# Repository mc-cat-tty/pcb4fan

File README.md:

# pcb4fan

## Schematic

## Render 3D
<p>

 <br>

 <br>
 
</p>

## Etching mask

## Results

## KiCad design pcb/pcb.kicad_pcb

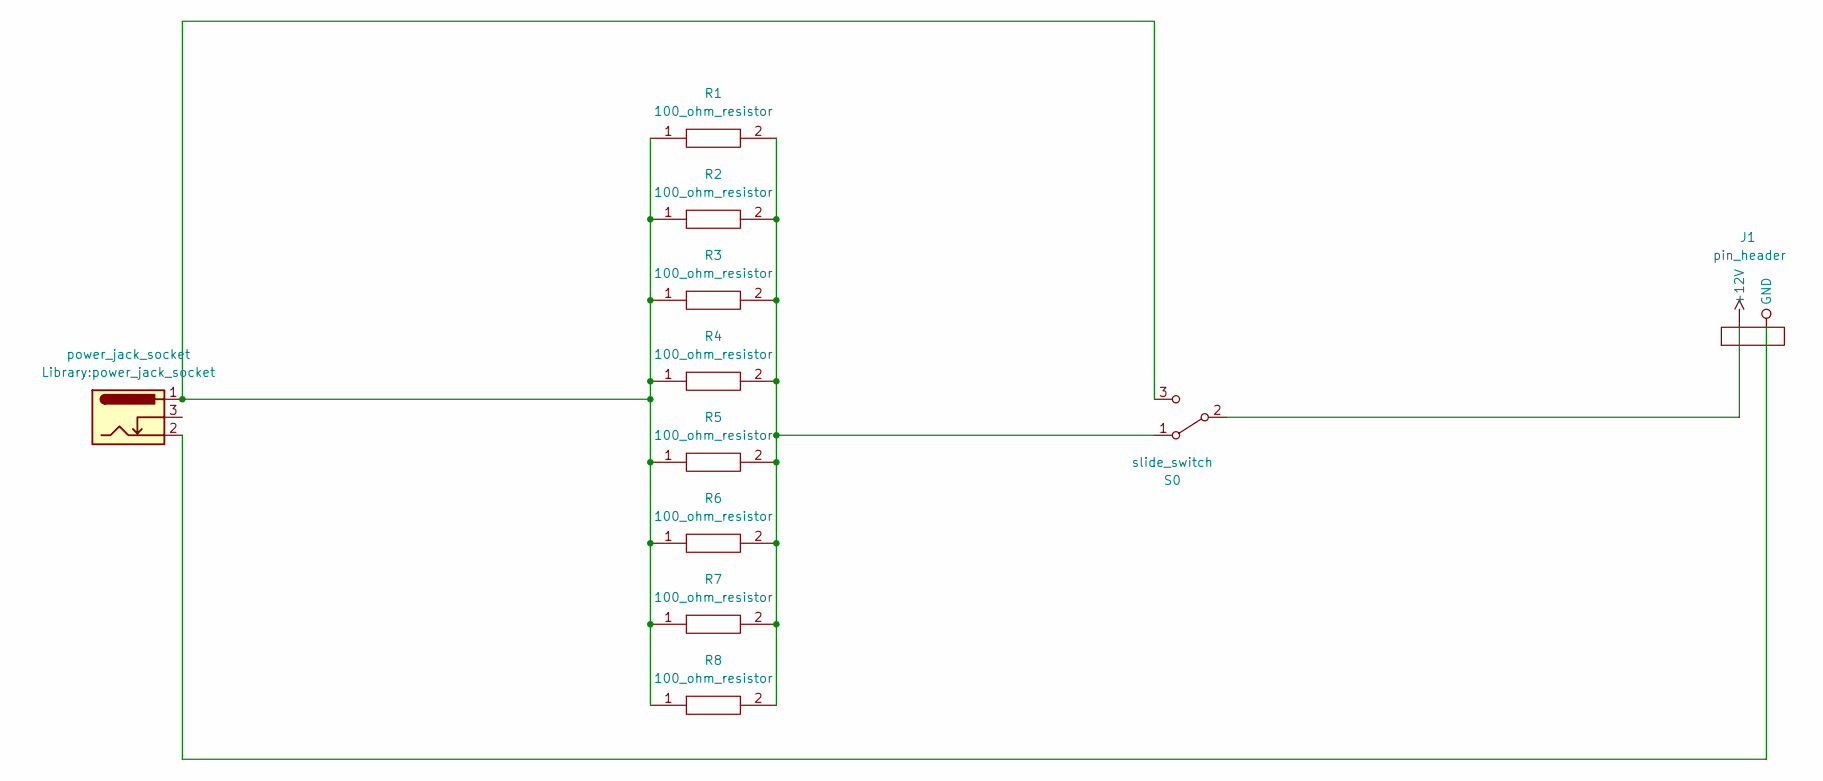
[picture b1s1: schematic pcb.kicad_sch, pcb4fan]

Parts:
J1: pin_header
J2: power_jack_socket
R1, R2, R3, R4, R5, R6, R7, R8: 100_ohm_resistor
S0: slide_switch

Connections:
unnamed: J1.1 (+12V), S0.2 (B)
unnamed: J1.2 (GND), J2.2
unnamed: J2.1, R1.1, R2.1, R3.1, R4.1, R5.1, R6.1, R7.1, R8.1, S0.3 (C)
unnamed: R1.2, R2.2, R3.2, R4.2, R5.2, R6.2, R7.2, R8.2, S0.1 (A)

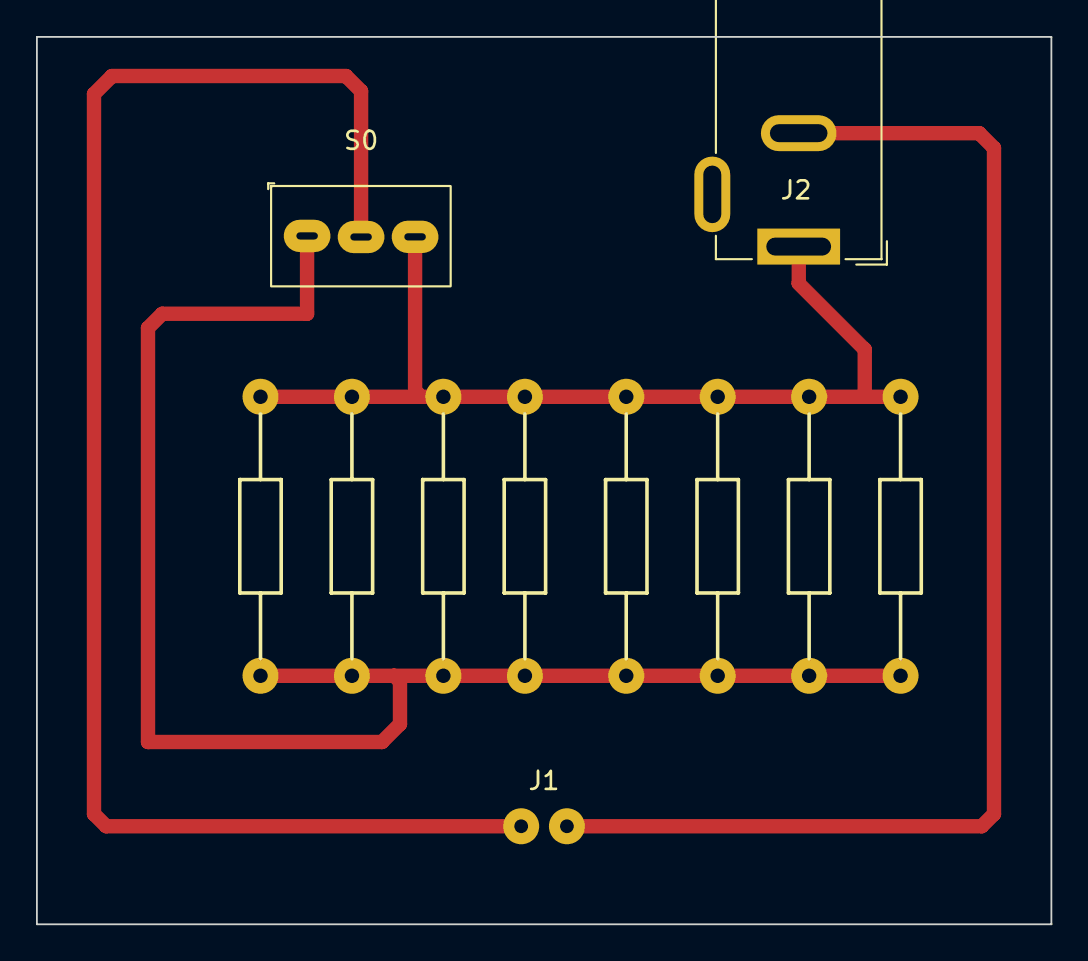
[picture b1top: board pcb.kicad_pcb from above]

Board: 2 copper layers, 56.4 x 49.3 mm, 11 parts (0 on the bottom side), 4 nets.

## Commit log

2022-01-21 add components
2022-01-22 turn absolute paths into relative paths
2022-01-22 create 2-pin connector footprint
2022-01-22 refine 2-pins connector footprint
2022-01-22 add 3d model
2022-01-22 add 2-pins connector schematic
2022-01-22 add resistor to components
2022-01-22 draw schematic
2022-01-22 add pcb
2022-01-22 add 3d render
2022-01-22 add details to sheets
2022-01-22 change resistor footprint
2022-01-22 labels cleanout
2022-01-22 add pcb and schematic pdf
2022-01-22 add etching masks
2022-01-22 bigger pin header footprint
2022-01-22 export flipped etching masks
2022-01-23 add 3D model to outfiles
2022-01-24 upload real images
2022-01-24 readme file
2022-01-24 remove duplicate
2022-01-24 change size!
2022-01-24 resize images
2022-01-24 show images side by side
2022-01-24 images side by side
2022-01-24 percentage width
2022-01-24 change image format
